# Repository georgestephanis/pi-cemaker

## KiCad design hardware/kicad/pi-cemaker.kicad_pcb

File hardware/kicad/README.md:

# KiCad project: Pi-cemaker Lite (DRAFT)

Generated, not hand-drawn. Edit `gen/design.py`, then run `gen/build.sh`. Reasoning for every guess is in [`../DECISIONS.md`](../DECISIONS.md).

| File | What |
|---|---|
| `gen/design.py` | Single source of truth: parts, values, footprints, pin-to-net map |
| `gen/gen_sch.py` | Writes `pi-cemaker.kicad_sch` + `pi-cemaker.kicad_sym` + `gen/netlist.json` |
| `gen/gen_fp.py` | Writes the hand-built BQ25792 footprint (`pi-cemaker.pretty/`) |
| `gen/gen_pcb.py` | Writes `pi-cemaker.kicad_pcb` (placement, outline, GND pours) |
| `gen/gen_bom.py` | Writes `../BOM_DRAFT.csv` |

## State (2026-10-01)
- **Schematic:** 110 parts, 51 nets, **KiCad ERC: 0 violations**. Layout is one flat sheet, grouped by function, with labels instead of wires (readable, not pretty). ERC clean only means the netlist is consistent; it does not mean the circuit is right.
- **PCB:** 112 × 78 mm, 2 layers, all parts placed, autorouted with Freerouting then GND-filled. **38 connections remain unrouted**, plus silk/courtyard/clearance violations. Power nets are 0.75–1.0 mm traces (borderline for 3–4 A on 1 oz). Not reviewed by a human.
- **Fab files: deliberately not produced.** `kicad-cli pcb export gerbers` works, but the BQ25792 footprint is a guess from an image, passives are unselected, and the board is not fully routed (DECISIONS D18–D20).

## Next steps, in order
1. Replace `VQFN-HR-29_RQM0029A_4x4mm` with TI's official footprint; compare U3's footprint with TI's DRR drawing.
2. Pick real MPNs; check DC-bias derating and inductor Isat; stock check at the assembler.
3. Re-place by hand (switching loops tight, inductors next to SW pins), route power by hand, then autoroute the rest; get DRC to zero.
4. Human review of the schematic against the two datasheets; then bring-up per `../DESIGN_FOR_TEST.md`.
5. Only then export Gerbers/CPL.

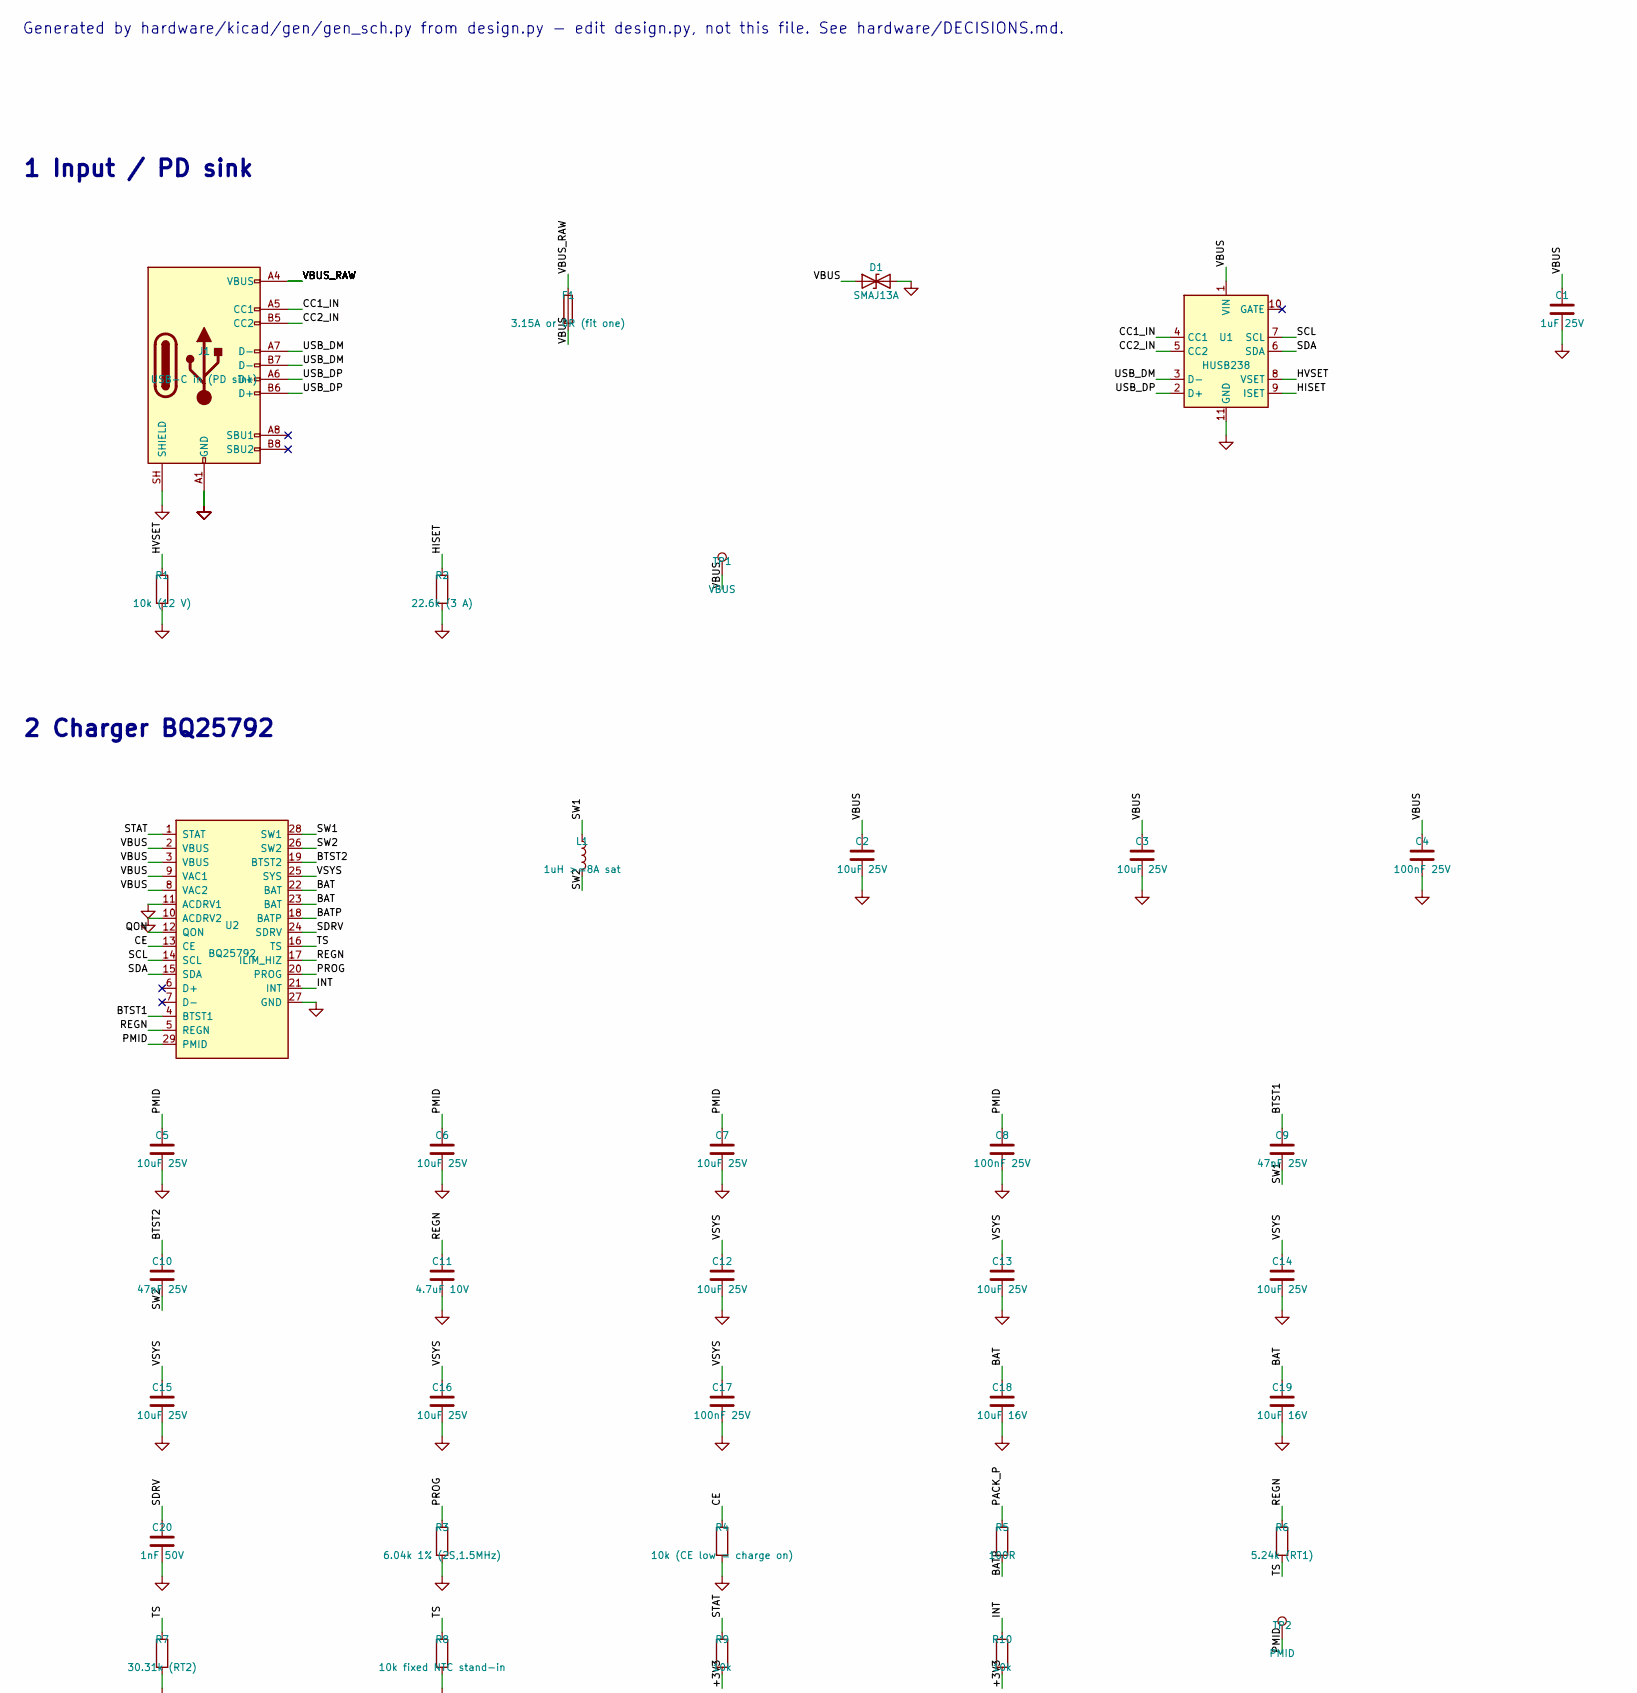
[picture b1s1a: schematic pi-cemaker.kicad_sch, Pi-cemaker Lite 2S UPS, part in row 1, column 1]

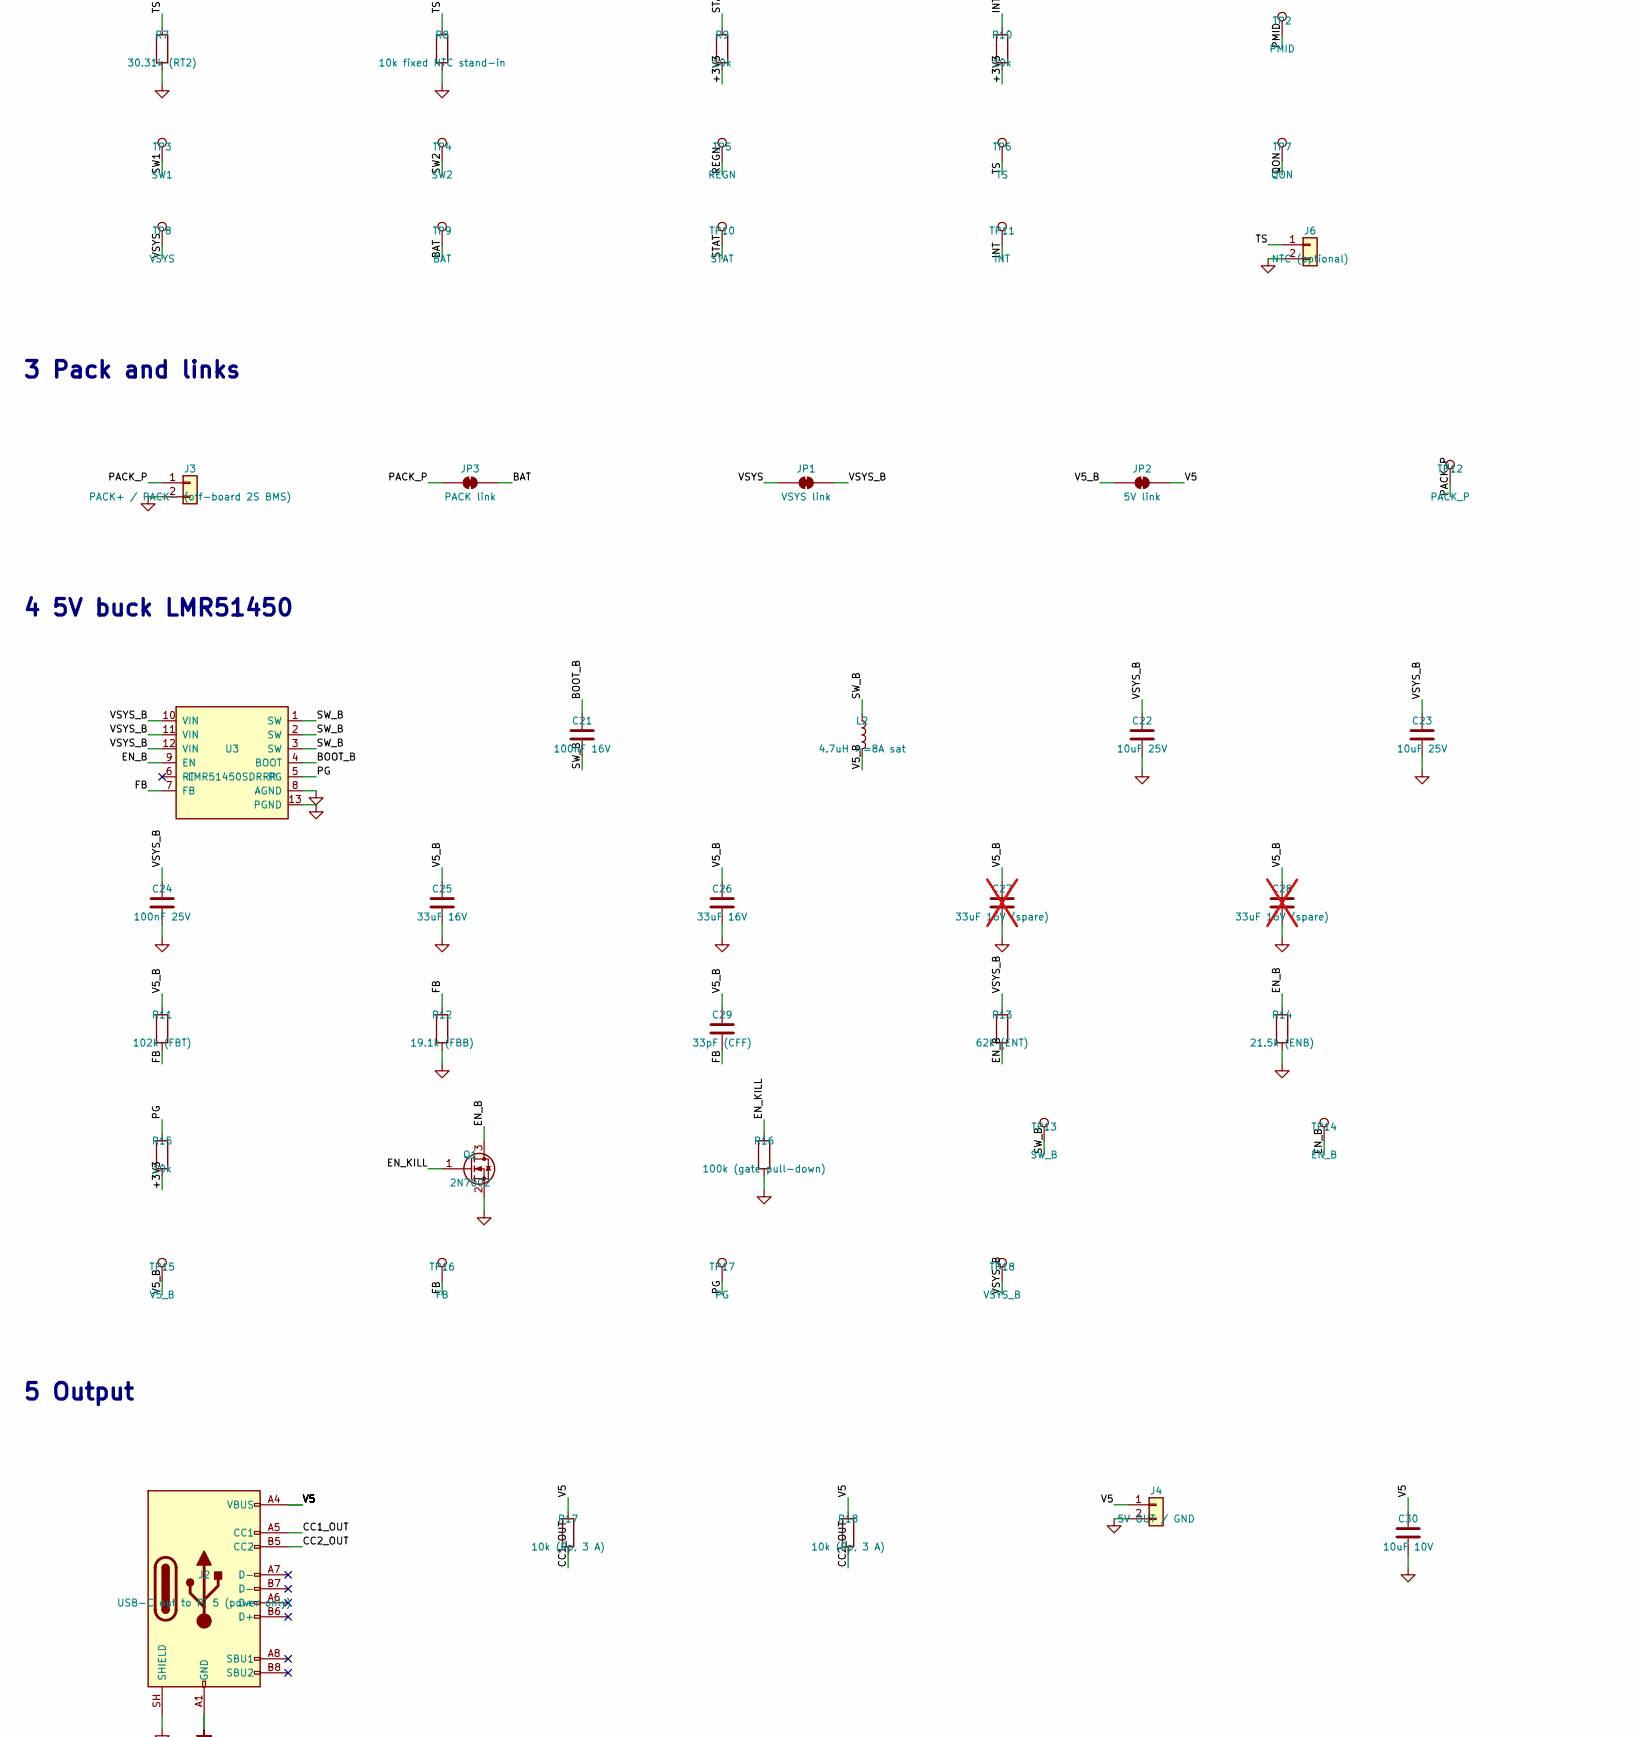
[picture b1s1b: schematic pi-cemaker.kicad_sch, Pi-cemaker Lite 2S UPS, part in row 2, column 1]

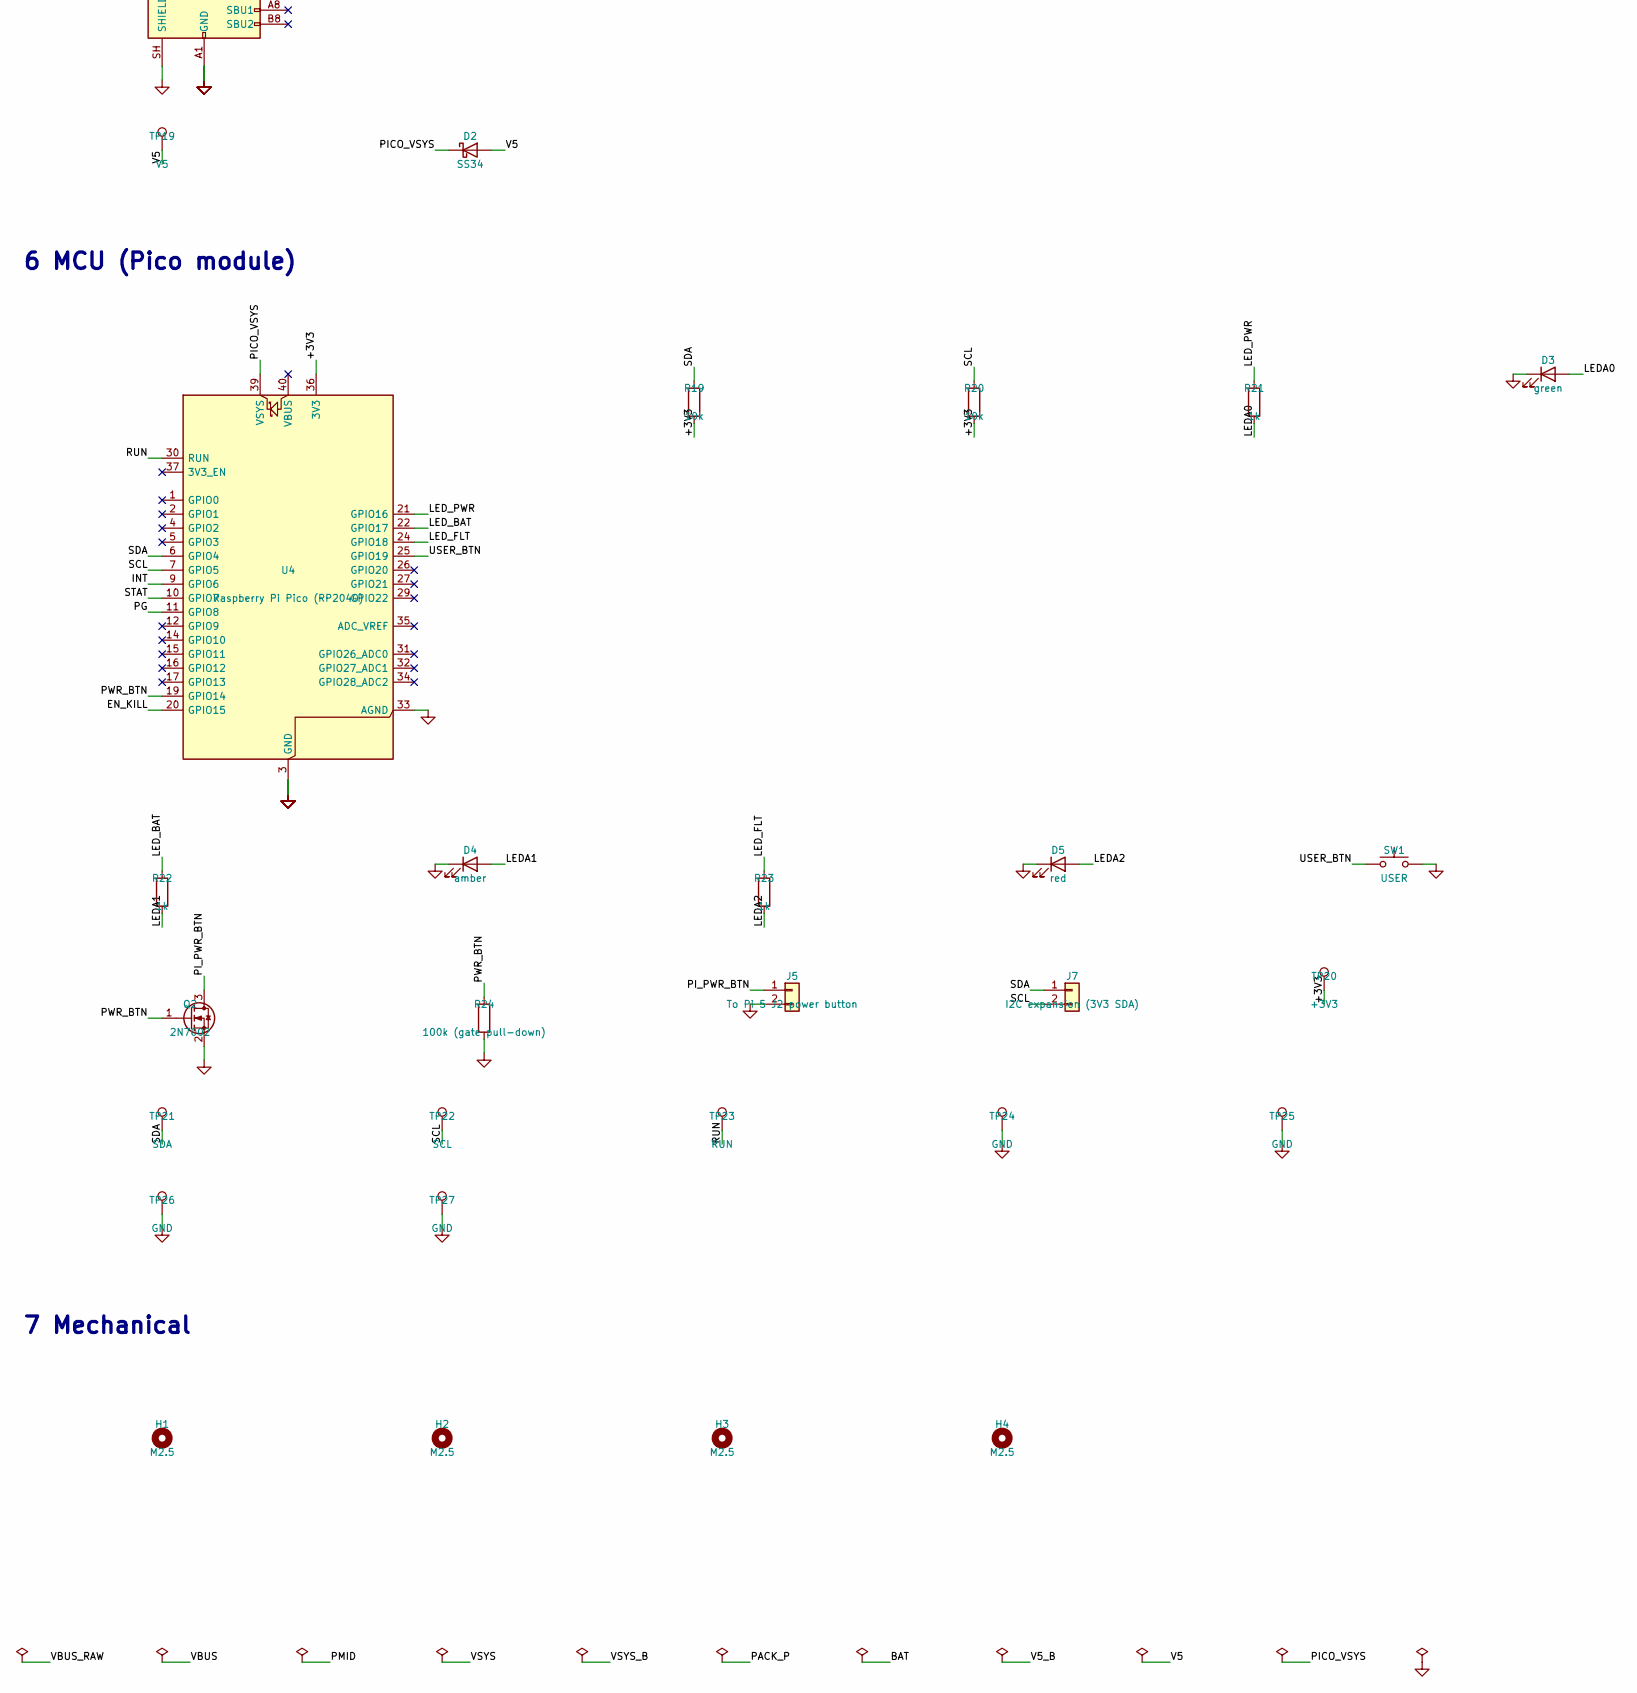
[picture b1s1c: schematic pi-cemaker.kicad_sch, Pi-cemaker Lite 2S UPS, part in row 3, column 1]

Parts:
C1: 1uF 25V; C_0603_1608Metric
C2, C3, C5, C6, C7, C12, C13, C14, C15, C16, C22, C23: 10uF 25V; C_1206_3216Metric
C4, C8, C17, C24: 100nF 25V; C_0603_1608Metric
C9, C10: 47nF 25V; C_0603_1608Metric
C11: 4.7uF 10V; C_0805_2012Metric
C18, C19: 10uF 16V; C_1206_3216Metric
C20: 1nF 50V; C_0603_1608Metric
C21: 100nF 16V; C_0603_1608Metric
C25, C26: 33uF 16V; C_1210_3225Metric
C27, C28: 33uF 16V (spare); C_1210_3225Metric; not fitted
C29: 33pF (CFF); C_0603_1608Metric
C30: 10uF 10V; C_0805_2012Metric
D1: SMAJ13A; D_SMA; MPN SMAJ13A (verify clamp vs 30 V parts)
D2: SS34; D_SMA; MPN SS34 (verify)
D3: green; LED_0603_1608Metric
D4: amber; LED_0603_1608Metric
D5: red; LED_0603_1608Metric
F1: 3.15A or 0R (fit one); Fuse_1206_3216Metric
H1, H2, H3, H4: M2.5; MountingHole_2.7mm_M2.5_Pad
J1: USB-C in (PD sink); USB_C_Receptacle_GCT_USB4105-xx-A_16P_TopMnt_Horizontal; MPN GCT USB4105-GF-A (verify)
J2: USB-C out to Pi 5 (power only); USB_C_Receptacle_GCT_USB4105-xx-A_16P_TopMnt_Horizontal; MPN GCT USB4105-GF-A (verify)
J3: PACK+ / PACK- (off-board 2S BMS); TerminalBlock_Phoenix_MKDS-1,5-2_1x02_P5.00mm_Horizontal
J4: 5V OUT / GND; TerminalBlock_Phoenix_MKDS-1,5-2_1x02_P5.00mm_Horizontal
J5: To Pi 5 J2 power button; PinHeader_1x02_P2.54mm_Vertical
J6: NTC (optional); PinHeader_1x02_P2.54mm_Vertical
J7: I2C expansion (3V3 SDA); PinHeader_1x02_P2.54mm_Vertical
JP1: VSYS link; SolderJumper-2_P1.3mm_Bridged_RoundedPad1.0x1.5mm
JP2: 5V link; SolderJumper-2_P1.3mm_Bridged_RoundedPad1.0x1.5mm
JP3: PACK link; SolderJumper-2_P1.3mm_Bridged_RoundedPad1.0x1.5mm
L1: 1uH >=8A sat; L_Bourns_SRP7028A_7.3x6.6mm; MPN 1 uH, Isat>=8 A shielded (verify)
L2: 4.7uH >=8A sat; L_Bourns_SRP7028A_7.3x6.6mm; MPN 4.7 uH, Isat>=8 A (verify)
Q1, Q2: 2N7002; SOT-23
R1: 10k (12 V); R_0603_1608Metric
R2: 22.6k (3 A); R_0603_1608Metric
R3: 6.04k 1% (2S,1.5MHz); R_0603_1608Metric
R4: 10k (CE low = charge on); R_0603_1608Metric
R5: 100R; R_0603_1608Metric
R6: 5.24k (RT1); R_0603_1608Metric
R7: 30.31k (RT2); R_0603_1608Metric
R8: 10k fixed NTC stand-in; R_0603_1608Metric
R9, R10, R15, R19, R20: 10k; R_0603_1608Metric
R11: 102k (FBT); R_0603_1608Metric
R12: 19.1k (FBB); R_0603_1608Metric
R13: 62k (ENT); R_0603_1608Metric
R14: 21.5k (ENB); R_0603_1608Metric
R16, R24: 100k (gate pull-down); R_0603_1608Metric
R17, R18: 10k (Rp, 3 A); R_0603_1608Metric
R21, R22, R23: 1k; R_0603_1608Metric
SW1: USER; SW_SPST_PTS810
TP1: VBUS; TestPoint_Pad_D1.0mm
TP2: PMID; TestPoint_Pad_D1.0mm
TP3: SW1; TestPoint_Pad_D1.0mm
TP4: SW2; TestPoint_Pad_D1.0mm
TP5: REGN; TestPoint_Pad_D1.0mm
TP6: TS; TestPoint_Pad_D1.0mm
TP7: QON; TestPoint_Pad_D1.0mm
TP8: VSYS; TestPoint_Pad_D1.0mm
TP9: BAT; TestPoint_Pad_D1.0mm
TP10: STAT; TestPoint_Pad_D1.0mm
TP11: INT; TestPoint_Pad_D1.0mm
TP12: PACK_P; TestPoint_Pad_D1.0mm
TP13: SW_B; TestPoint_Pad_D1.0mm
TP14: EN_B; TestPoint_Pad_D1.0mm
TP15: V5_B; TestPoint_Pad_D1.0mm
TP16: FB; TestPoint_Pad_D1.0mm
TP17: PG; TestPoint_Pad_D1.0mm
TP18: VSYS_B; TestPoint_Pad_D1.0mm
TP19: V5; TestPoint_Pad_D1.0mm
TP20: +3V3; TestPoint_Pad_D1.0mm
TP21: SDA; TestPoint_Pad_D1.0mm
TP22: SCL; TestPoint_Pad_D1.0mm
TP23: RUN; TestPoint_Pad_D1.0mm
TP24, TP25, TP26, TP27: GND; TestPoint_Pad_D1.0mm
U1: HUSB238; DFN-10-1EP_3x3mm_P0.5mm_EP1.65x2.38mm; MPN Hynetek HUSB238 DFN-10 (verify package)
U2: BQ25792; VQFN-HR-29_RQM0029A_4x4mm; MPN TI BQ25792RQMR
U3: LMR51450SDRRR; WSON-12-1EP_3x3mm_P0.5mm_EP1.5x2.5mm; MPN TI LMR51450SDRRR
U4: Raspberry Pi Pico (RP2040); RaspberryPi_Pico_Common_THT; MPN Pico (headers hand-fitted)

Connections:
+3V3: R9.2, R10.2, R15.2, R19.2, R20.2, TP20.1, U4.36 (3V3)
BAT: C18.1, C19.1, JP3.2 (B), TP9.1, U2.22 (BAT), U2.23 (BAT)
BATP: R5.2, U2.18 (BATP)
BOOT_B: C21.1, U3.4 (BOOT)
BTST1: C9.1, U2.4 (BTST1)
BTST2: C10.1, U2.19 (BTST2)
CC1_IN: J1.A5 (CC1), U1.4 (CC1)
CC1_OUT: J2.A5 (CC1), R17.2
CC2_IN: J1.B5 (CC2), U1.5 (CC2)
CC2_OUT: J2.B5 (CC2), R18.2
CE: R4.1, U2.13 (CE)
EN_B: Q1.3 (D), R13.2, R14.1, TP14.1, U3.9 (EN)
EN_KILL: Q1.1 (G), R16.1, U4.20 (GPIO15)
FB: C29.2, R11.2, R12.1, TP16.1, U3.7 (FB)
GND: C1.2, C2.2, C3.2, C4.2, C5.2, C6.2, C7.2, C8.2, C11.2, C12.2, C13.2, C14.2, C15.2, C16.2, C17.2, C18.2, C19.2, C20.2, C22.2, C23.2, C24.2, C25.2, C26.2, C27.2, C28.2, C30.2, D1.2 (A2), D3.1 (K), D4.1 (K), D5.1 (K), J1.A1 (GND), J1.A12 (GND), J1.B1 (GND), J1.B12 (GND), J1.SH (SHIELD), J2.A1 (GND), J2.A12 (GND), J2.B1 (GND), J2.B12 (GND), J2.SH (SHIELD), J3.2, J4.2, J5.2, J6.2, Q1.2 (S), Q2.2 (S), R1.2, R2.2, R3.2, R4.2, R7.2, R8.2, R12.2, R14.2, R16.2, R24.2, SW1.2, TP24.1, TP25.1, TP26.1, TP27.1, U1.11 (GND), U2.10 (ACDRV2), U2.11 (ACDRV1), U2.27 (GND), U3.8 (AGND), U3.13 (PGND), U4.3 (GND), U4.8 (GND), U4.13 (GND), U4.18 (GND), U4.23 (GND), U4.28 (GND), U4.33 (AGND), U4.38 (GND)
HISET: R2.1, U1.9 (ISET)
HVSET: R1.1, U1.8 (VSET)
INT: R10.1, TP11.1, U2.21 (INT), U4.9 (GPIO6)
LEDA0: D3.2 (A), R21.2
LEDA1: D4.2 (A), R22.2
LEDA2: D5.2 (A), R23.2
LED_BAT: R22.1, U4.22 (GPIO17)
LED_FLT: R23.1, U4.24 (GPIO18)
LED_PWR: R21.1, U4.21 (GPIO16)
PACK_P: J3.1, JP3.1 (A), R5.1, TP12.1
PG: R15.1, TP17.1, U3.5 (PG), U4.11 (GPIO8)
PICO_VSYS: D2.1 (K), U4.39 (VSYS)
PI_PWR_BTN: J5.1, Q2.3 (D)
PMID: C5.1, C6.1, C7.1, C8.1, TP2.1, U2.29 (PMID)
PROG: R3.1, U2.20 (PROG)
PWR_BTN: Q2.1 (G), R24.1, U4.19 (GPIO14)
QON: TP7.1, U2.12 (QON)
REGN: C11.1, R6.1, TP5.1, U2.5 (REGN), U2.17 (ILIM_HIZ)
RUN: TP23.1, U4.30 (RUN)
SCL: J7.2, R20.1, TP22.1, U1.7 (SCL), U2.14 (SCL), U4.7 (GPIO5)
SDA: J7.1, R19.1, TP21.1, U1.6 (SDA), U2.15 (SDA), U4.6 (GPIO4)
SDRV: C20.1, U2.24 (SDRV)
STAT: R9.1, TP10.1, U2.1 (STAT), U4.10 (GPIO7)
SW1: C9.2, L1.1, TP3.1, U2.28 (SW1)
SW2: C10.2, L1.2, TP4.1, U2.26 (SW2)
SW_B: C21.2, L2.1, TP13.1, U3.1 (SW), U3.2 (SW), U3.3 (SW)
TS: J6.1, R6.2, R7.1, R8.1, TP6.1, U2.16 (TS)
USB_DM: J1.A7 (D-), J1.B7 (D-), U1.3 (D-)
USB_DP: J1.A6 (D+), J1.B6 (D+), U1.2 (D+)
USER_BTN: SW1.1, U4.25 (GPIO19)
V5: C30.1, D2.2 (A), J2.A4 (VBUS), J2.A9 (VBUS), J2.B4 (VBUS), J2.B9 (VBUS), J4.1, JP2.2 (B), R17.1, R18.1, TP19.1
V5_B: C25.1, C26.1, C27.1, C28.1, C29.1, JP2.1 (A), L2.2, R11.1, TP15.1
VBUS: C1.1, C2.1, C3.1, C4.1, D1.1 (A1), F1.2, TP1.1, U1.1 (VIN), U2.2 (VBUS), U2.3 (VBUS), U2.8 (VAC2), U2.9 (VAC1)
VBUS_RAW: F1.1, J1.A4 (VBUS), J1.A9 (VBUS), J1.B4 (VBUS), J1.B9 (VBUS)
VSYS: C12.1, C13.1, C14.1, C15.1, C16.1, C17.1, JP1.1 (A), TP8.1, U2.25 (SYS)
VSYS_B: C22.1, C23.1, C24.1, JP1.2 (B), R13.1, TP18.1, U3.10 (VIN), U3.11 (VIN), U3.12 (VIN)

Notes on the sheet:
Generated by hardware/kicad/gen/gen_sch.py from design.py - edit design.py, not this file. See hardware/DECISIONS.md.
1 Input / PD sink
2 Charger BQ25792
3 Pack and links
4 5V buck LMR51450
5 Output
6 MCU (Pico module)
7 Mechanical

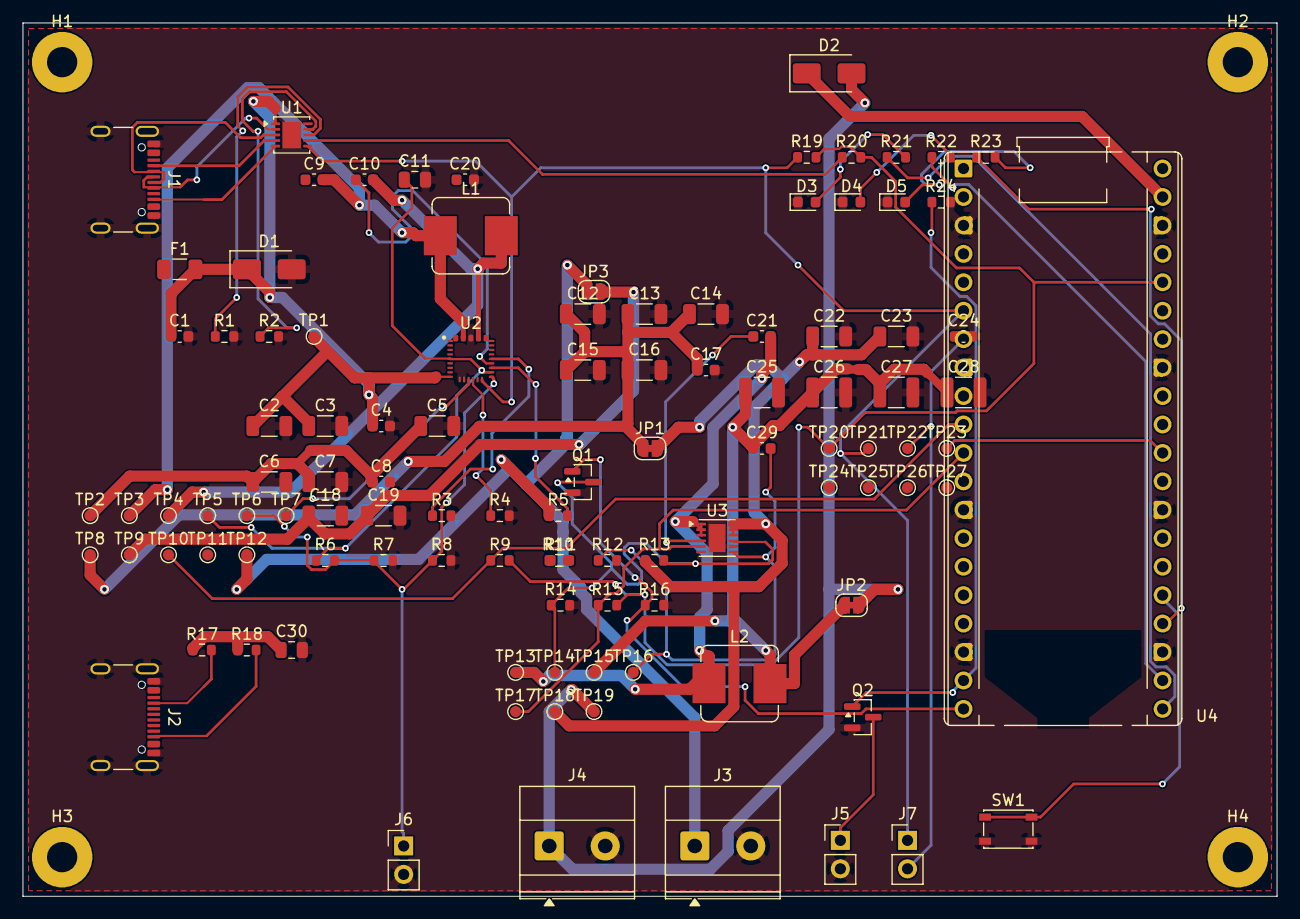
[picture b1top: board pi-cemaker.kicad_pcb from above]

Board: 2 copper layers, 112.0 x 78.0 mm, 110 parts (0 on the bottom side), 51 nets.

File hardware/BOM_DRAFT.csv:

Refs,Qty,Value,Footprint,MPN,DNP,Status
C1,1,1uF 25V,Capacitor_SMD:C_0603_1608Metric,,,UNVERIFIED
C10 C9,2,47nF 25V,Capacitor_SMD:C_0603_1608Metric,,,UNVERIFIED
C11,1,4.7uF 10V,Capacitor_SMD:C_0805_2012Metric,,,UNVERIFIED
C12 C13 C14 C15 C16 C2 C22 C23 C3 C5 C6 C7,12,10uF 25V,Capacitor_SMD:C_1206_3216Metric,,,UNVERIFIED
C17 C24 C4 C8,4,100nF 25V,Capacitor_SMD:C_0603_1608Metric,,,UNVERIFIED
C18 C19,2,10uF 16V,Capacitor_SMD:C_1206_3216Metric,,,UNVERIFIED
C20,1,1nF 50V,Capacitor_SMD:C_0603_1608Metric,,,UNVERIFIED
C21,1,100nF 16V,Capacitor_SMD:C_0603_1608Metric,,,UNVERIFIED
C25 C26,2,33uF 16V,Capacitor_SMD:C_1210_3225Metric,,,UNVERIFIED
C27 C28,2,33uF 16V (spare),Capacitor_SMD:C_1210_3225Metric,,DNP,UNVERIFIED
C29,1,33pF (CFF),Capacitor_SMD:C_0603_1608Metric,,,UNVERIFIED
C30,1,10uF 10V,Capacitor_SMD:C_0805_2012Metric,,,UNVERIFIED
D1,1,SMAJ13A,Diode_SMD:D_SMA,SMAJ13A (verify clamp vs 30 V parts),,UNVERIFIED
D2,1,SS34,Diode_SMD:D_SMA,SS34 (verify),,UNVERIFIED
D3,1,green,LED_SMD:LED_0603_1608Metric,,,UNVERIFIED
D4,1,amber,LED_SMD:LED_0603_1608Metric,,,UNVERIFIED
D5,1,red,LED_SMD:LED_0603_1608Metric,,,UNVERIFIED
F1,1,3.15A or 0R (fit one),Fuse:Fuse_1206_3216Metric,,,UNVERIFIED
H1 H2 H3 H4,4,M2.5,MountingHole:MountingHole_2.7mm_M2.5_Pad,,,UNVERIFIED
J1,1,USB-C in (PD sink),Connector_USB:USB_C_Receptacle_GCT_USB4105-xx-A_16P_TopMnt_Horizontal,GCT USB4105-GF-A (verify),,UNVERIFIED
J2,1,USB-C out to Pi 5 (power only),Connector_USB:USB_C_Receptacle_GCT_USB4105-xx-A_16P_TopMnt_Horizontal,GCT USB4105-GF-A (verify),,UNVERIFIED
J3,1,PACK+ / PACK- (off-board 2S BMS),"TerminalBlock_Phoenix:TerminalBlock_Phoenix_MKDS-1,5-2_1x02_P5.00mm_Horizontal",,,UNVERIFIED
J4,1,5V OUT / GND,"TerminalBlock_Phoenix:TerminalBlock_Phoenix_MKDS-1,5-2_1x02_P5.00mm_Horizontal",,,UNVERIFIED
J5,1,To Pi 5 J2 power button,Connector_PinHeader_2.54mm:PinHeader_1x02_P2.54mm_Vertical,,,UNVERIFIED
J6,1,NTC (optional),Connector_PinHeader_2.54mm:PinHeader_1x02_P2.54mm_Vertical,,,UNVERIFIED
J7,1,I2C expansion (3V3 SDA),Connector_PinHeader_2.54mm:PinHeader_1x02_P2.54mm_Vertical,,,UNVERIFIED
JP1,1,VSYS link,Jumper:SolderJumper-2_P1.3mm_Bridged_RoundedPad1.0x1.5mm,,,UNVERIFIED
JP2,1,5V link,Jumper:SolderJumper-2_P1.3mm_Bridged_RoundedPad1.0x1.5mm,,,UNVERIFIED
JP3,1,PACK link,Jumper:SolderJumper-2_P1.3mm_Bridged_RoundedPad1.0x1.5mm,,,UNVERIFIED
L1,1,1uH >=8A sat,Inductor_SMD:L_Bourns_SRP7028A_7.3x6.6mm,"1 uH, Isat>=8 A shielded (verify)",,UNVERIFIED
L2,1,4.7uH >=8A sat,Inductor_SMD:L_Bourns_SRP7028A_7.3x6.6mm,"4.7 uH, Isat>=8 A (verify)",,UNVERIFIED
Q1 Q2,2,2N7002,Package_TO_SOT_SMD:SOT-23,,,UNVERIFIED
R1,1,10k (12 V),Resistor_SMD:R_0603_1608Metric,,,UNVERIFIED
R10 R15 R19 R20 R9,5,10k,Resistor_SMD:R_0603_1608Metric,,,UNVERIFIED
R11,1,102k (FBT),Resistor_SMD:R_0603_1608Metric,,,UNVERIFIED
R12,1,19.1k (FBB),Resistor_SMD:R_0603_1608Metric,,,UNVERIFIED
R13,1,62k (ENT),Resistor_SMD:R_0603_1608Metric,,,UNVERIFIED
R14,1,21.5k (ENB),Resistor_SMD:R_0603_1608Metric,,,UNVERIFIED
R16 R24,2,100k (gate pull-down),Resistor_SMD:R_0603_1608Metric,,,UNVERIFIED
R17 R18,2,"10k (Rp, 3 A)",Resistor_SMD:R_0603_1608Metric,,,UNVERIFIED
R2,1,22.6k (3 A),Resistor_SMD:R_0603_1608Metric,,,UNVERIFIED
R21 R22 R23,3,1k,Resistor_SMD:R_0603_1608Metric,,,UNVERIFIED
R3,1,"6.04k 1% (2S,1.5MHz)",Resistor_SMD:R_0603_1608Metric,,,UNVERIFIED
R4,1,10k (CE low = charge on),Resistor_SMD:R_0603_1608Metric,,,UNVERIFIED
R5,1,100R,Resistor_SMD:R_0603_1608Metric,,,UNVERIFIED
R6,1,5.24k (RT1),Resistor_SMD:R_0603_1608Metric,,,UNVERIFIED
R7,1,30.31k (RT2),Resistor_SMD:R_0603_1608Metric,,,UNVERIFIED
R8,1,10k fixed NTC stand-in,Resistor_SMD:R_0603_1608Metric,,,UNVERIFIED
SW1,1,USER,Button_Switch_SMD:SW_SPST_PTS810,,,UNVERIFIED
TP1,1,VBUS,TestPoint:TestPoint_Pad_D1.0mm,,,UNVERIFIED
TP10,1,STAT,TestPoint:TestPoint_Pad_D1.0mm,,,UNVERIFIED
TP11,1,INT,TestPoint:TestPoint_Pad_D1.0mm,,,UNVERIFIED
TP12,1,PACK_P,TestPoint:TestPoint_Pad_D1.0mm,,,UNVERIFIED
TP13,1,SW_B,TestPoint:TestPoint_Pad_D1.0mm,,,UNVERIFIED
TP14,1,EN_B,TestPoint:TestPoint_Pad_D1.0mm,,,UNVERIFIED
TP15,1,V5_B,TestPoint:TestPoint_Pad_D1.0mm,,,UNVERIFIED
TP16,1,FB,TestPoint:TestPoint_Pad_D1.0mm,,,UNVERIFIED
TP17,1,PG,TestPoint:TestPoint_Pad_D1.0mm,,,UNVERIFIED
TP18,1,VSYS_B,TestPoint:TestPoint_Pad_D1.0mm,,,UNVERIFIED
TP19,1,V5,TestPoint:TestPoint_Pad_D1.0mm,,,UNVERIFIED
TP2,1,PMID,TestPoint:TestPoint_Pad_D1.0mm,,,UNVERIFIED
TP20,1,+3V3,TestPoint:TestPoint_Pad_D1.0mm,,,UNVERIFIED
TP21,1,SDA,TestPoint:TestPoint_Pad_D1.0mm,,,UNVERIFIED
TP22,1,SCL,TestPoint:TestPoint_Pad_D1.0mm,,,UNVERIFIED
TP23,1,RUN,TestPoint:TestPoint_Pad_D1.0mm,,,UNVERIFIED
TP24 TP25 TP26 TP27,4,GND,TestPoint:TestPoint_Pad_D1.0mm,,,UNVERIFIED
TP3,1,SW1,TestPoint:TestPoint_Pad_D1.0mm,,,UNVERIFIED
TP4,1,SW2,TestPoint:TestPoint_Pad_D1.0mm,,,UNVERIFIED
TP5,1,REGN,TestPoint:TestPoint_Pad_D1.0mm,,,UNVERIFIED
TP6,1,TS,TestPoint:TestPoint_Pad_D1.0mm,,,UNVERIFIED
TP7,1,QON,TestPoint:TestPoint_Pad_D1.0mm,,,UNVERIFIED
TP8,1,VSYS,TestPoint:TestPoint_Pad_D1.0mm,,,UNVERIFIED
TP9,1,BAT,TestPoint:TestPoint_Pad_D1.0mm,,,UNVERIFIED
U1,1,HUSB238,Package_DFN_QFN:DFN-10-1EP_3x3mm_P0.5mm_EP1.65x2.38mm,Hynetek HUSB238 DFN-10 (verify package),,UNVERIFIED
U2,1,BQ25792,pi-cemaker:VQFN-HR-29_RQM0029A_4x4mm,TI BQ25792RQMR,,MPN verified
U3,1,LMR51450SDRRR,Package_SON:WSON-12-1EP_3x3mm_P0.5mm_EP1.5x2.5mm,TI LMR51450SDRRR,,MPN verified
U4,1,Raspberry Pi Pico (RP2040),Module:RaspberryPi_Pico_Common_THT,Pico (headers hand-fitted),,MPN verified

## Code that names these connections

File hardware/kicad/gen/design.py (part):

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# ---------------------------------------------------------------- MCU
g = "6 MCU (Pico module)"
add("U4", "MCU_Module:RaspberryPi_Pico", "Raspberry Pi Pico (RP2040)", "Module:RaspberryPi_Pico_Common_THT",
    {"GND": "GND", "AGND": "GND", "3V3": "+3V3", "VSYS": "PICO_VSYS", "GPIO4": "SDA", "GPIO5": "SCL", "GPIO6": "INT",
     "GPIO7": "STAT", "GPIO8": "PG", "GPIO14": "PWR_BTN", "GPIO15": "EN_KILL", "GPIO16": "LED_PWR", "GPIO17": "LED_BAT",
     "GPIO18": "LED_FLT", "GPIO19": "USER_BTN", "RUN": "RUN"}, g, mpn="Pico (headers hand-fitted)",
    nc=["GPIO0", "GPIO1", "GPIO2", "GPIO3", "GPIO9", "GPIO10", "GPIO11", "GPIO12", "GPIO13", "GPIO20", "GPIO21",
        "GPIO22", "GPIO26_ADC0", "GPIO27_ADC1", "GPIO28_ADC2", "ADC_VREF", "3V3_EN", "VBUS"])
res("R19", "10k", "SDA", "+3V3", g); res("R20", "10k", "SCL", "+3V3", g)
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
